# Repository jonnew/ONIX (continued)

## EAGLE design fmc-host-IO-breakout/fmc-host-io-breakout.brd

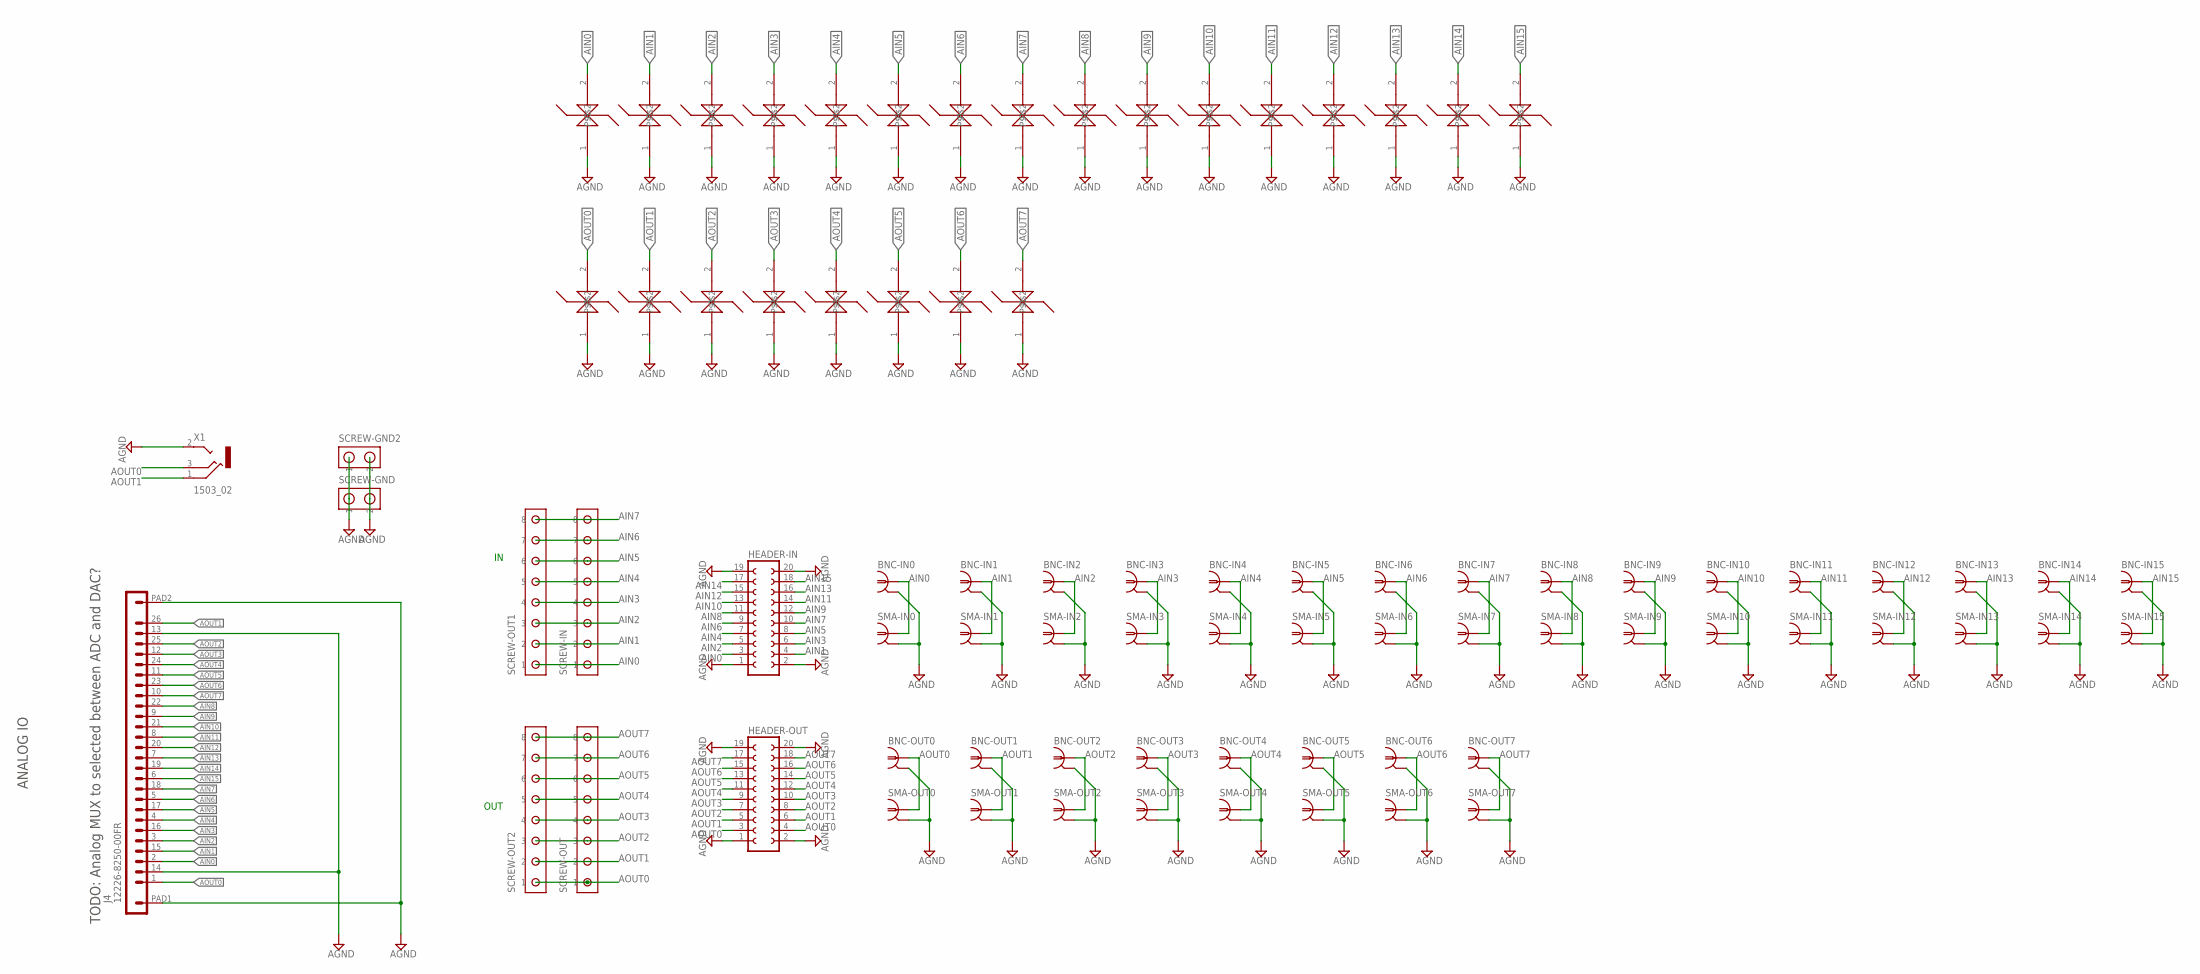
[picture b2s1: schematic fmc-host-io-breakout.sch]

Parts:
BNC-IN0, BNC-IN1, BNC-IN2, BNC-IN3, BNC-IN4, BNC-IN5, BNC-IN6, BNC-IN7, BNC-IN8, BNC-IN9, BNC-IN10, BNC-IN11, BNC-IN12, BNC-IN13, BNC-IN14, BNC-IN15: COAX_B35N61; B35N61
BNC-OUT0, BNC-OUT1, BNC-OUT2, BNC-OUT3, BNC-OUT4, BNC-OUT5, BNC-OUT6, BNC-OUT7: COAX_B35N61; B35N61
HEADER-IN: FE10-2
HEADER-OUT: FE10-2
J4: 12226-8250-00FR; 12226-82X0-00XX
SCREW-GND, SCREW-GND2: SCREW2
SCREW-IN: SCREW8
SCREW-OUT, SCREW-OUT1, SCREW-OUT2: SCREW8
SMA-IN0, SMA-IN1, SMA-IN2, SMA-IN3, SMA-IN4, SMA-IN5, SMA-IN6, SMA-IN7, SMA-IN8, SMA-IN9, SMA-IN10, SMA-IN11, SMA-IN12, SMA-IN13, SMA-IN14, SMA-IN15: COAX_SMA-VERT; SMA_JACK_142-0701-201
SMA-OUT0, SMA-OUT1, SMA-OUT2, SMA-OUT3, SMA-OUT4, SMA-OUT5, SMA-OUT6, SMA-OUT7: COAX_SMA-VERT; SMA_JACK_142-0701-201
U$1, U$2, U$3, U$4, U$5, U$6, U$7, U$8, U$9, U$10, U$11, U$12, U$13, U$14, U$15, U$16, U$17, U$18, U$19, U$20, U$21, U$22, U$23, U$24: DIODE-ESD-BIDIRECTIONALDO-214AA; DIOC7026X260
X1: 1503_02

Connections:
AIN0: BNC-IN0.1, HEADER-IN.3, J4.2, SCREW-IN.1, SCREW-OUT1.1, SMA-IN0.CLK (1), U$1.2
AIN1: BNC-IN1.1, HEADER-IN.4, J4.15, SCREW-IN.2, SCREW-OUT1.2, SMA-IN1.CLK (1), U$2.2
AIN2: BNC-IN2.1, HEADER-IN.5, J4.3, SCREW-IN.3, SCREW-OUT1.3, SMA-IN2.CLK (1), U$3.2
AIN3: BNC-IN3.1, HEADER-IN.6, J4.16, SCREW-IN.4, SCREW-OUT1.4, SMA-IN3.CLK (1), U$4.2
AIN4: BNC-IN4.1, HEADER-IN.7, J4.4, SCREW-IN.5, SCREW-OUT1.5, SMA-IN4.CLK (1), U$5.2
AIN5: BNC-IN5.1, HEADER-IN.8, J4.17, SCREW-IN.6, SCREW-OUT1.6, SMA-IN5.CLK (1), U$6.2
AIN6: BNC-IN6.1, HEADER-IN.9, J4.5, SCREW-IN.7, SCREW-OUT1.7, SMA-IN6.CLK (1), U$7.2
AIN7: BNC-IN7.1, HEADER-IN.10, J4.18, SCREW-IN.8, SCREW-OUT1.8, SMA-IN7.CLK (1), U$8.2
AIN8: BNC-IN8.1, HEADER-IN.11, J4.22, SMA-IN8.CLK (1), U$17.2
AIN9: BNC-IN9.1, HEADER-IN.12, J4.9, SMA-IN9.CLK (1), U$18.2
AIN10: BNC-IN10.1, HEADER-IN.13, J4.21, SMA-IN10.CLK (1), U$19.2
AIN11: BNC-IN11.1, HEADER-IN.14, J4.8, SMA-IN11.CLK (1), U$20.2
AIN12: BNC-IN12.1, HEADER-IN.15, J4.20, SMA-IN12.CLK (1), U$21.2
AIN13: BNC-IN13.1, HEADER-IN.16, J4.7, SMA-IN13.CLK (1), U$22.2
AIN14: BNC-IN14.1, HEADER-IN.17, J4.19, SMA-IN14.CLK (1), U$23.2
AIN15: BNC-IN15.1, HEADER-IN.18, J4.6, SMA-IN15.CLK (1), U$24.2
AOUT0: BNC-OUT0.1, HEADER-OUT.3, HEADER-OUT.4, J4.1, SCREW-OUT.1, SCREW-OUT2.1, SMA-OUT0.CLK (1), U$9.2, X1.3
AOUT1: BNC-OUT1.1, HEADER-OUT.5, HEADER-OUT.6, J4.26, SCREW-OUT.2, SCREW-OUT2.2, SMA-OUT1.CLK (1), U$10.2, X1.1
AOUT2: BNC-OUT2.1, HEADER-OUT.7, HEADER-OUT.8, J4.25, SCREW-OUT.3, SCREW-OUT2.3, SMA-OUT2.CLK (1), U$11.2
AOUT3: BNC-OUT3.1, HEADER-OUT.9, HEADER-OUT.10, J4.12, SCREW-OUT.4, SCREW-OUT2.4, SMA-OUT3.CLK (1), U$12.2
AOUT4: BNC-OUT4.1, HEADER-OUT.11, HEADER-OUT.12, J4.24, SCREW-OUT.5, SCREW-OUT2.5, SMA-OUT4.CLK (1), U$13.2
AOUT5: BNC-OUT5.1, HEADER-OUT.13, HEADER-OUT.14, J4.11, SCREW-OUT.6, SCREW-OUT2.6, SMA-OUT5.CLK (1), U$14.2
AOUT6: BNC-OUT6.1, HEADER-OUT.15, HEADER-OUT.16, J4.23, SCREW-OUT.7, SCREW-OUT2.7, SMA-OUT6.CLK (1), U$15.2
AOUT7: BNC-OUT7.1, HEADER-OUT.17, HEADER-OUT.18, J4.10, SCREW-OUT.8, SCREW-OUT2.8, SMA-OUT7.CLK (1), U$16.2
GND: BNC-IN0.2, BNC-IN0.3 (2), BNC-IN0.4 (2), BNC-IN0.5 (2), BNC-IN1.2, BNC-IN1.3 (2), BNC-IN1.4 (2), BNC-IN1.5 (2), BNC-IN2.2, BNC-IN2.3 (2), BNC-IN2.4 (2), BNC-IN2.5 (2), BNC-IN3.2, BNC-IN3.3 (2), BNC-IN3.4 (2), BNC-IN3.5 (2), BNC-IN4.2, BNC-IN4.3 (2), BNC-IN4.4 (2), BNC-IN4.5 (2), BNC-IN5.2, BNC-IN5.3 (2), BNC-IN5.4 (2), BNC-IN5.5 (2), BNC-IN6.2, BNC-IN6.3 (2), BNC-IN6.4 (2), BNC-IN6.5 (2), BNC-IN7.2, BNC-IN7.3 (2), BNC-IN7.4 (2), BNC-IN7.5 (2), BNC-IN8.2, BNC-IN8.3 (2), BNC-IN8.4 (2), BNC-IN8.5 (2), BNC-IN9.2, BNC-IN9.3 (2), BNC-IN9.4 (2), BNC-IN9.5 (2), BNC-IN10.2, BNC-IN10.3 (2), BNC-IN10.4 (2), BNC-IN10.5 (2), BNC-IN11.2, BNC-IN11.3 (2), BNC-IN11.4 (2), BNC-IN11.5 (2), BNC-IN12.2, BNC-IN12.3 (2), BNC-IN12.4 (2), BNC-IN12.5 (2), BNC-IN13.2, BNC-IN13.3 (2), BNC-IN13.4 (2), BNC-IN13.5 (2), BNC-IN14.2, BNC-IN14.3 (2), BNC-IN14.4 (2), BNC-IN14.5 (2), BNC-IN15.2, BNC-IN15.3 (2), BNC-IN15.4 (2), BNC-IN15.5 (2), BNC-OUT0.2, BNC-OUT0.3 (2), BNC-OUT0.4 (2), BNC-OUT0.5 (2), BNC-OUT1.2, BNC-OUT1.3 (2), BNC-OUT1.4 (2), BNC-OUT1.5 (2), BNC-OUT2.2, BNC-OUT2.3 (2), BNC-OUT2.4 (2), BNC-OUT2.5 (2), BNC-OUT3.2, BNC-OUT3.3 (2), BNC-OUT3.4 (2), BNC-OUT3.5 (2), BNC-OUT4.2, BNC-OUT4.3 (2), BNC-OUT4.4 (2), BNC-OUT4.5 (2), BNC-OUT5.2, BNC-OUT5.3 (2), BNC-OUT5.4 (2), BNC-OUT5.5 (2), BNC-OUT6.2, BNC-OUT6.3 (2), BNC-OUT6.4 (2), BNC-OUT6.5 (2), BNC-OUT7.2, BNC-OUT7.3 (2), BNC-OUT7.4 (2), BNC-OUT7.5 (2), HEADER-IN.1, HEADER-IN.2, HEADER-IN.19, HEADER-IN.20, HEADER-OUT.1, HEADER-OUT.2, HEADER-OUT.19, HEADER-OUT.20, J4.13, J4.14, J4.PAD1, J4.PAD2, SCREW-GND.P$1 (1), SCREW-GND.P$2 (2), SCREW-GND2.P$1 (1), SCREW-GND2.P$2 (2), SMA-IN0.GND$1 (2), SMA-IN0.GND$2 (2), SMA-IN0.GND$3 (2), SMA-IN0.GND$4 (2), SMA-IN1.GND$1 (2), SMA-IN1.GND$2 (2), SMA-IN1.GND$3 (2), SMA-IN1.GND$4 (2), SMA-IN2.GND$1 (2), SMA-IN2.GND$2 (2), SMA-IN2.GND$3 (2), SMA-IN2.GND$4 (2), SMA-IN3.GND$1 (2), SMA-IN3.GND$2 (2), SMA-IN3.GND$3 (2), SMA-IN3.GND$4 (2), SMA-IN4.GND$1 (2), SMA-IN4.GND$2 (2), SMA-IN4.GND$3 (2), SMA-IN4.GND$4 (2), SMA-IN5.GND$1 (2), SMA-IN5.GND$2 (2), SMA-IN5.GND$3 (2), SMA-IN5.GND$4 (2), SMA-IN6.GND$1 (2), SMA-IN6.GND$2 (2), SMA-IN6.GND$3 (2), SMA-IN6.GND$4 (2), SMA-IN7.GND$1 (2), SMA-IN7.GND$2 (2), SMA-IN7.GND$3 (2), SMA-IN7.GND$4 (2), SMA-IN8.GND$1 (2), SMA-IN8.GND$2 (2), SMA-IN8.GND$3 (2), SMA-IN8.GND$4 (2), SMA-IN9.GND$1 (2), SMA-IN9.GND$2 (2), SMA-IN9.GND$3 (2), SMA-IN9.GND$4 (2), SMA-IN10.GND$1 (2), SMA-IN10.GND$2 (2), SMA-IN10.GND$3 (2), SMA-IN10.GND$4 (2), SMA-IN11.GND$1 (2), SMA-IN11.GND$2 (2), SMA-IN11.GND$3 (2), SMA-IN11.GND$4 (2), SMA-IN12.GND$1 (2), SMA-IN12.GND$2 (2), SMA-IN12.GND$3 (2), SMA-IN12.GND$4 (2), SMA-IN13.GND$1 (2), SMA-IN13.GND$2 (2), SMA-IN13.GND$3 (2), SMA-IN13.GND$4 (2), SMA-IN14.GND$1 (2), SMA-IN14.GND$2 (2), SMA-IN14.GND$3 (2), SMA-IN14.GND$4 (2), SMA-IN15.GND$1 (2), SMA-IN15.GND$2 (2), SMA-IN15.GND$3 (2), SMA-IN15.GND$4 (2), SMA-OUT0.GND$1 (2), SMA-OUT0.GND$2 (2), SMA-OUT0.GND$3 (2), SMA-OUT0.GND$4 (2), SMA-OUT1.GND$1 (2), SMA-OUT1.GND$2 (2), SMA-OUT1.GND$3 (2), SMA-OUT1.GND$4 (2), SMA-OUT2.GND$1 (2), SMA-OUT2.GND$2 (2), SMA-OUT2.GND$3 (2), SMA-OUT2.GND$4 (2), SMA-OUT3.GND$1 (2), SMA-OUT3.GND$2 (2), SMA-OUT3.GND$3 (2), SMA-OUT3.GND$4 (2), SMA-OUT4.GND$1 (2), SMA-OUT4.GND$2 (2), SMA-OUT4.GND$3 (2), SMA-OUT4.GND$4 (2), SMA-OUT5.GND$1 (2), SMA-OUT5.GND$2 (2), SMA-OUT5.GND$3 (2), SMA-OUT5.GND$4 (2), SMA-OUT6.GND$1 (2), SMA-OUT6.GND$2 (2), SMA-OUT6.GND$3 (2), SMA-OUT6.GND$4 (2), SMA-OUT7.GND$1 (2), SMA-OUT7.GND$2 (2), SMA-OUT7.GND$3 (2), SMA-OUT7.GND$4 (2), U$1.1, U$2.1, U$3.1, U$4.1, U$5.1, U$6.1, U$7.1, U$8.1, U$9.1, U$10.1, U$11.1, U$12.1, U$13.1, U$14.1, U$15.1, U$16.1, U$17.1, U$18.1, U$19.1, U$20.1, U$21.1, U$22.1, U$23.1, U$24.1, X1.2

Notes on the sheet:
TODO: Analog MUX to selected between ADC and DAC?
ANALOG IO
OUT

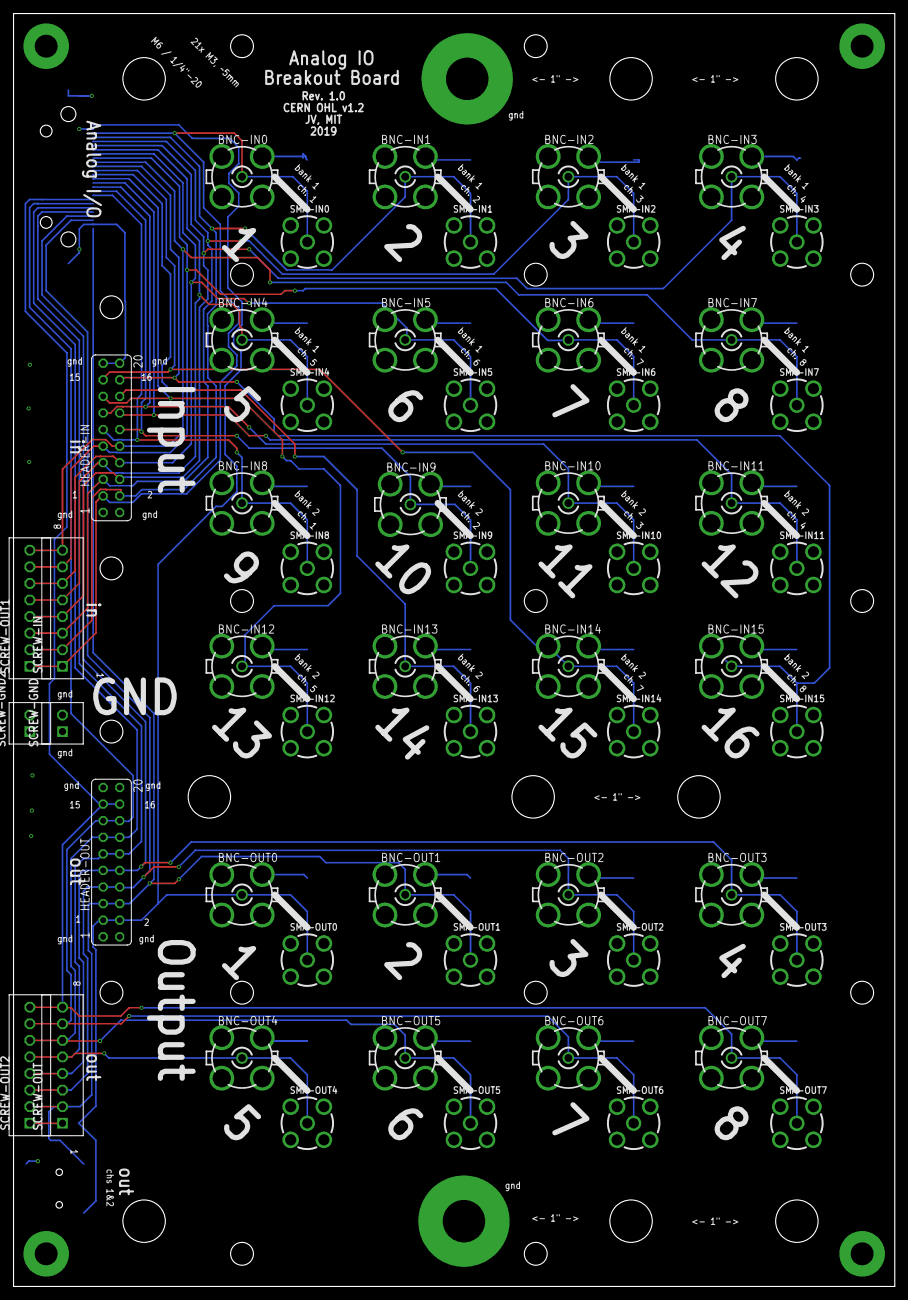
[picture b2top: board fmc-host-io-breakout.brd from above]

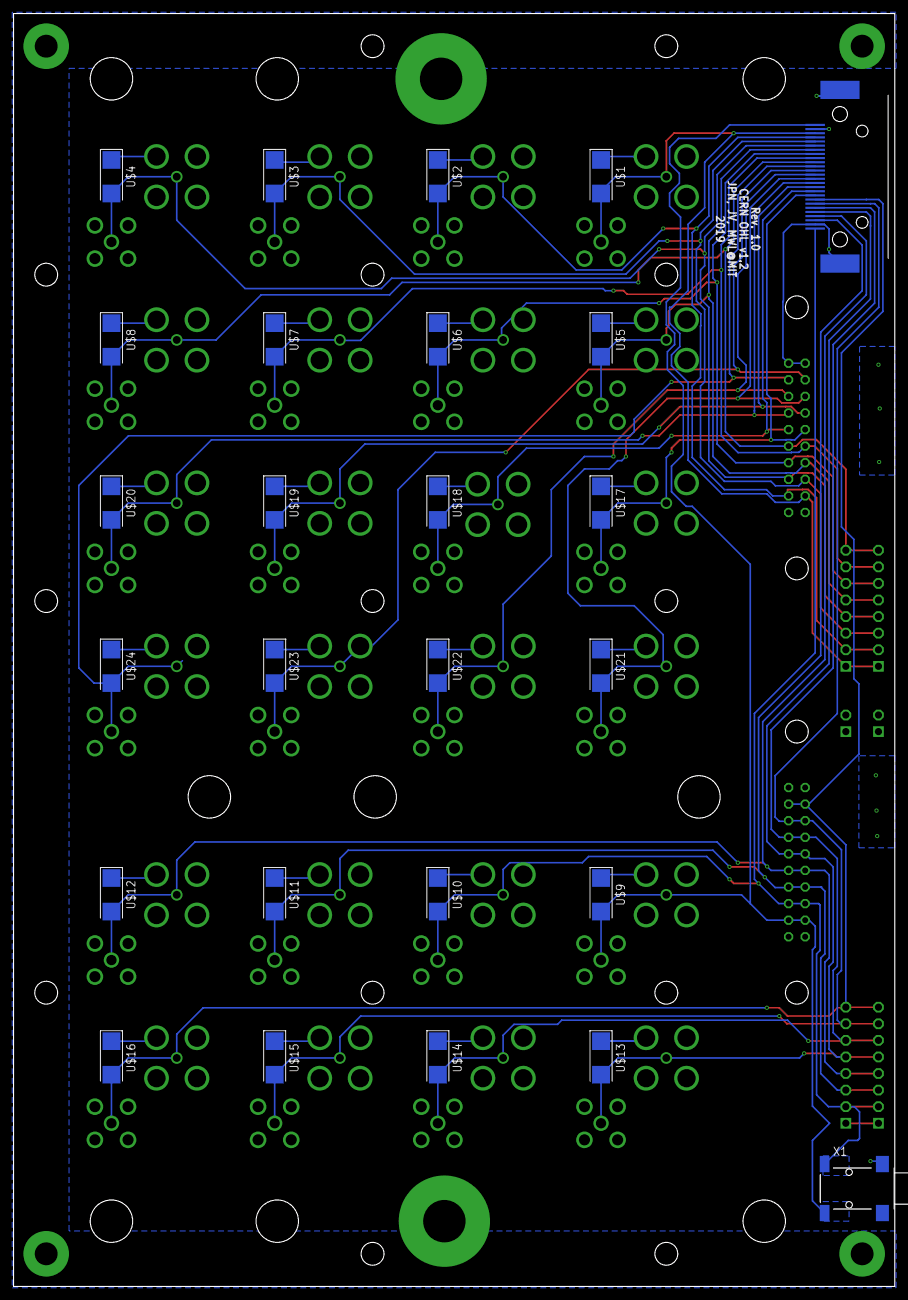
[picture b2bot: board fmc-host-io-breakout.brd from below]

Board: 2 copper layers, 135.0 x 195.0 mm, 82 parts (26 on the bottom side), 25 nets.

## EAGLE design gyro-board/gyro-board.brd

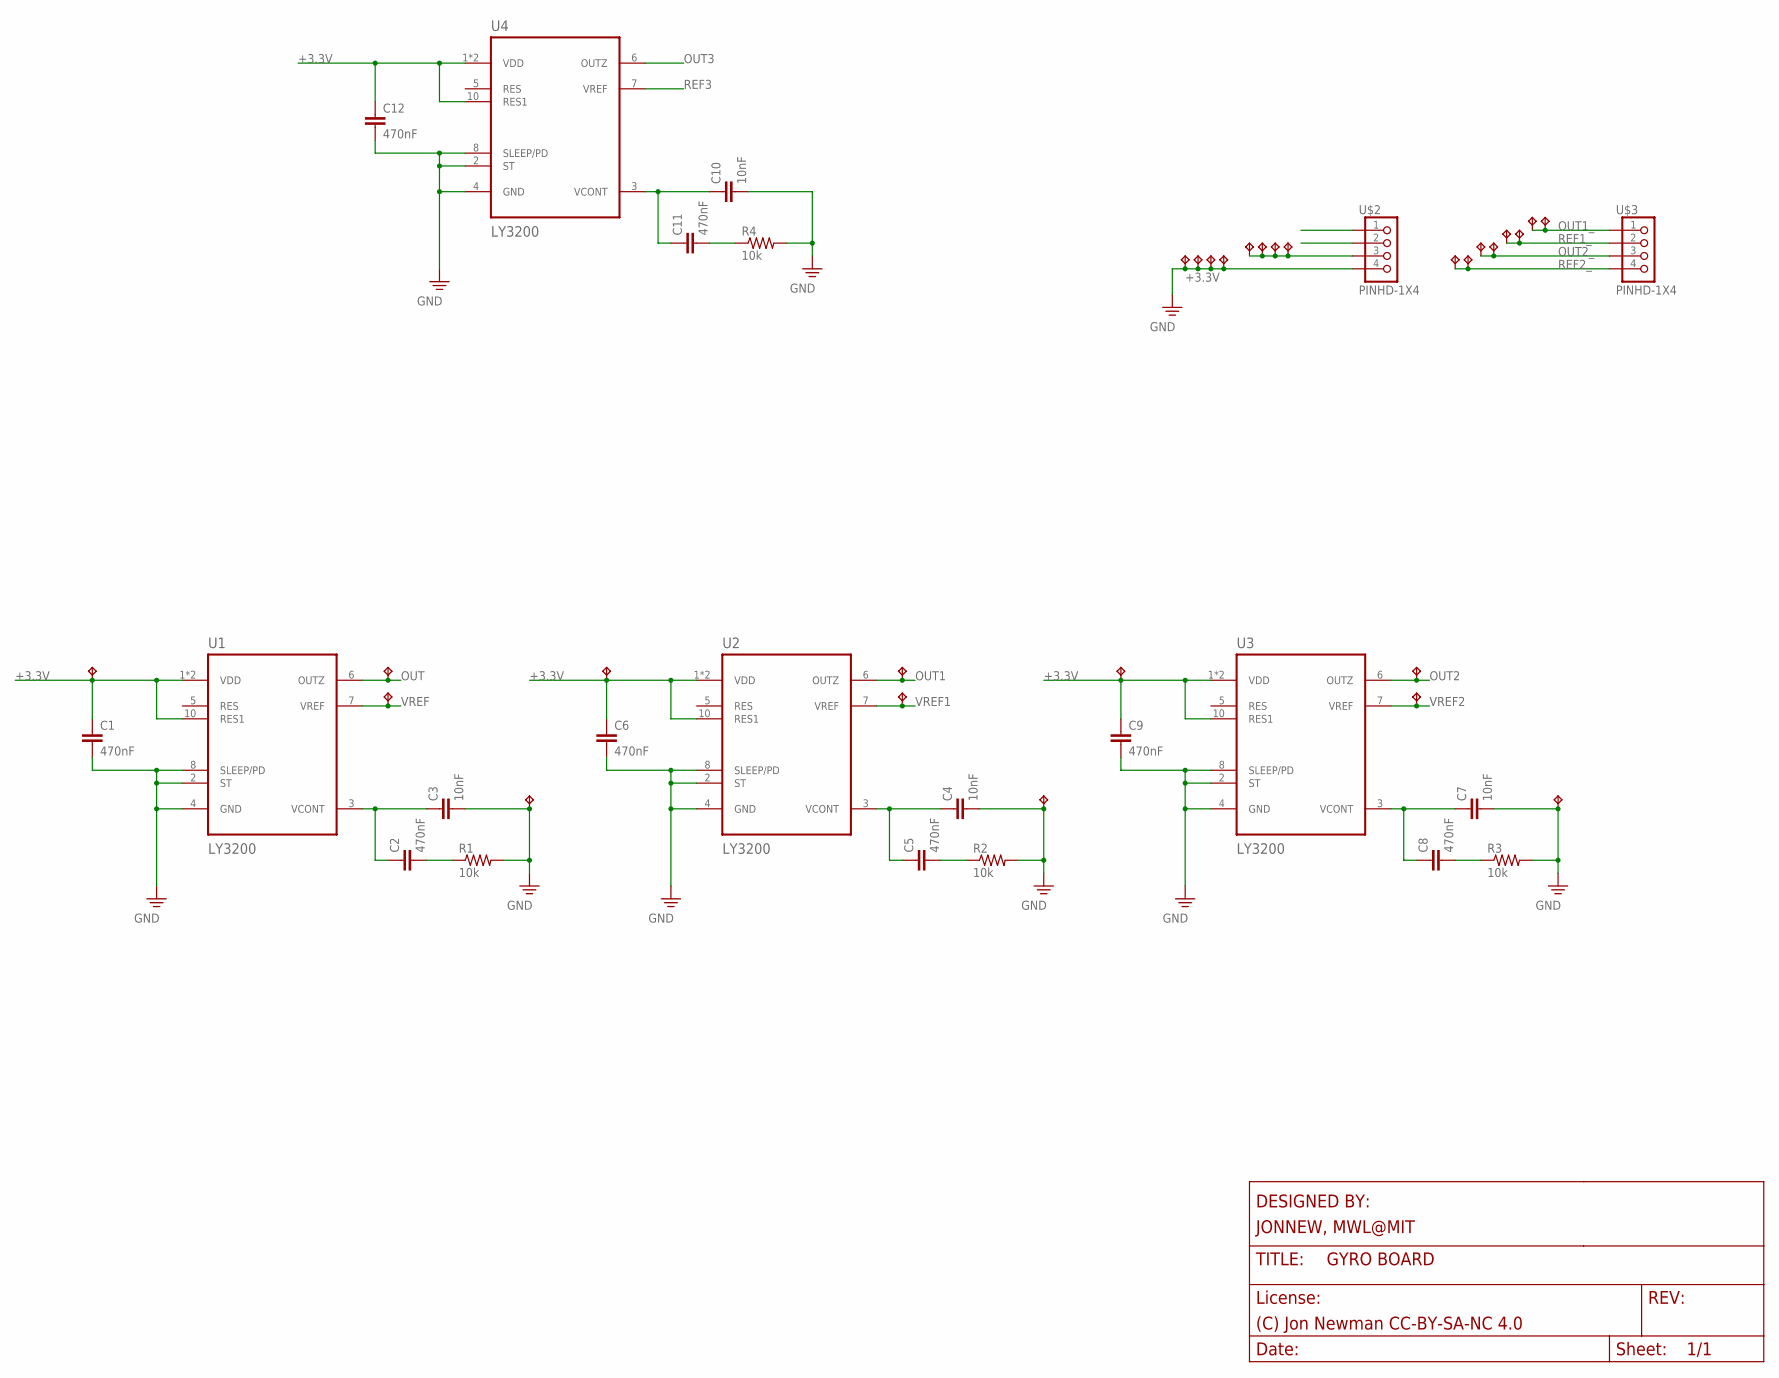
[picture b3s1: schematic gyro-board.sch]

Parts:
C1, C2, C5, C6, C8, C9, C11, C12: 470nF; 0201
C3, C4, C7, C10: 10nF; 0201
R1, R2, R3, R4: 10k; 0201
TP1, TP2, TP3, TP4, TP5, TP6, TP7, TP8, TP9, TP10, TP11, TP12, TP13, TP14, TP15, TP16, TP17, TP18, TP19, TP20, TP21, TP22, TP23, TP24, TP25, TP26, TP27, TP28: TPTP08SQ; TP08SQ
U1, U2, U3, U4: LY3200; LGA-10-COMPACT
U$2, U$3: PINHD-1X4; 1X04

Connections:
+3.3V: C1.1, C6.1, C9.1, C12.1, TP1.TP, TP4.TP, TP9.TP, TP25.TP, TP26.TP, TP27.TP, TP28.TP, U1.1 (VDD), U1.9 (VDD), U1.10 (RES1), U2.1 (VDD), U2.9 (VDD), U2.10 (RES1), U3.1 (VDD), U3.9 (VDD), U3.10 (RES1), U4.1 (VDD), U4.9 (VDD), U4.10 (RES1), U$2.3
GND: C1.2, C3.2, C4.2, C6.2, C7.2, C9.2, C10.2, C12.2, R1.2, R2.2, R3.2, R4.2, TP3.TP, TP7.TP, TP11.TP, TP13.TP, TP22.TP, TP23.TP, TP24.TP, U1.2 (ST), U1.4 (GND), U1.8 (SLEEP/PD), U2.2 (ST), U2.4 (GND), U2.8 (SLEEP/PD), U3.2 (ST), U3.4 (GND), U3.8 (SLEEP/PD), U4.2 (ST), U4.4 (GND), U4.8 (SLEEP/PD), U$2.4
unnamed: C4.1, C5.1, U2.3 (VCONT)
unnamed: C5.2, R2.1
unnamed: C2.1, C3.1, U1.3 (VCONT)
unnamed: C2.2, R1.1
unnamed: C7.1, C8.1, U3.3 (VCONT)
unnamed: C8.2, R3.1
unnamed: C10.1, C11.1, U4.3 (VCONT)
unnamed: C11.2, R4.1
OUT: TP2.TP, U1.6 (OUTZ)
OUT1: TP6.TP, U2.6 (OUTZ)
OUT1_: TP20.TP, TP21.TP, U$3.1
OUT2: TP10.TP, U3.6 (OUTZ)
OUT2_: TP16.TP, TP17.TP, U$3.3
OUT3: U4.6 (OUTZ), U$2.1
REF1_: TP18.TP, TP19.TP, U$3.2
REF2_: TP14.TP, TP15.TP, U$3.4
REF3: U4.7 (VREF), U$2.2
VREF: TP5.TP, U1.7 (VREF)
VREF1: TP8.TP, U2.7 (VREF)
VREF2: TP12.TP, U3.7 (VREF)

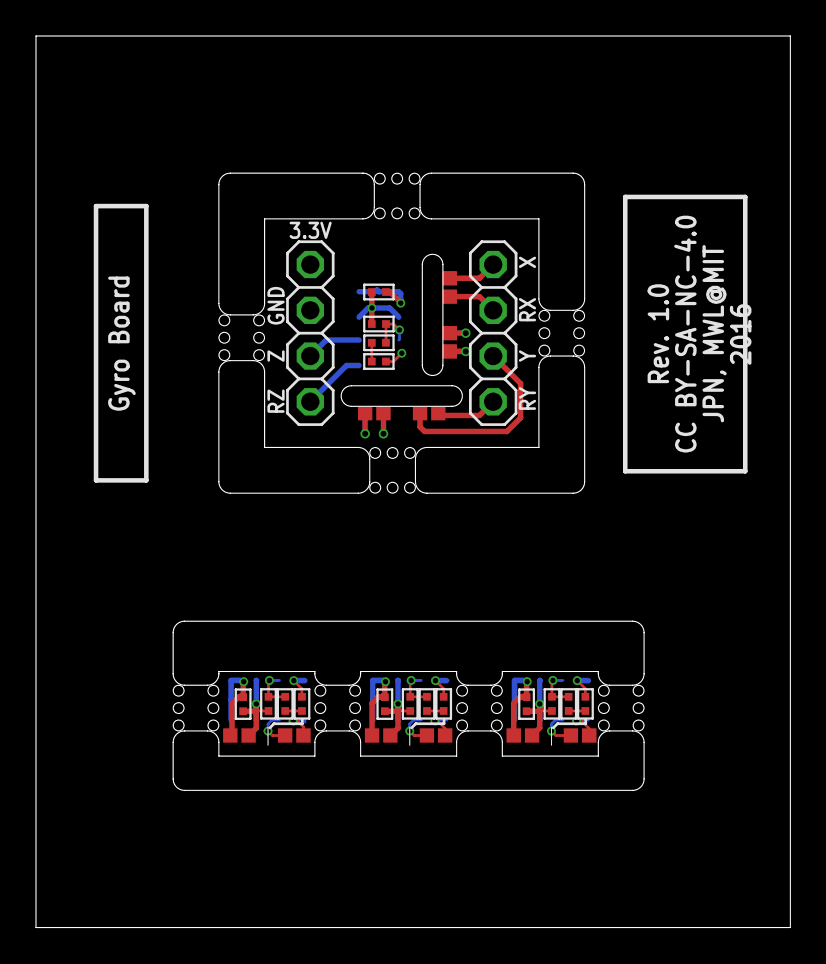
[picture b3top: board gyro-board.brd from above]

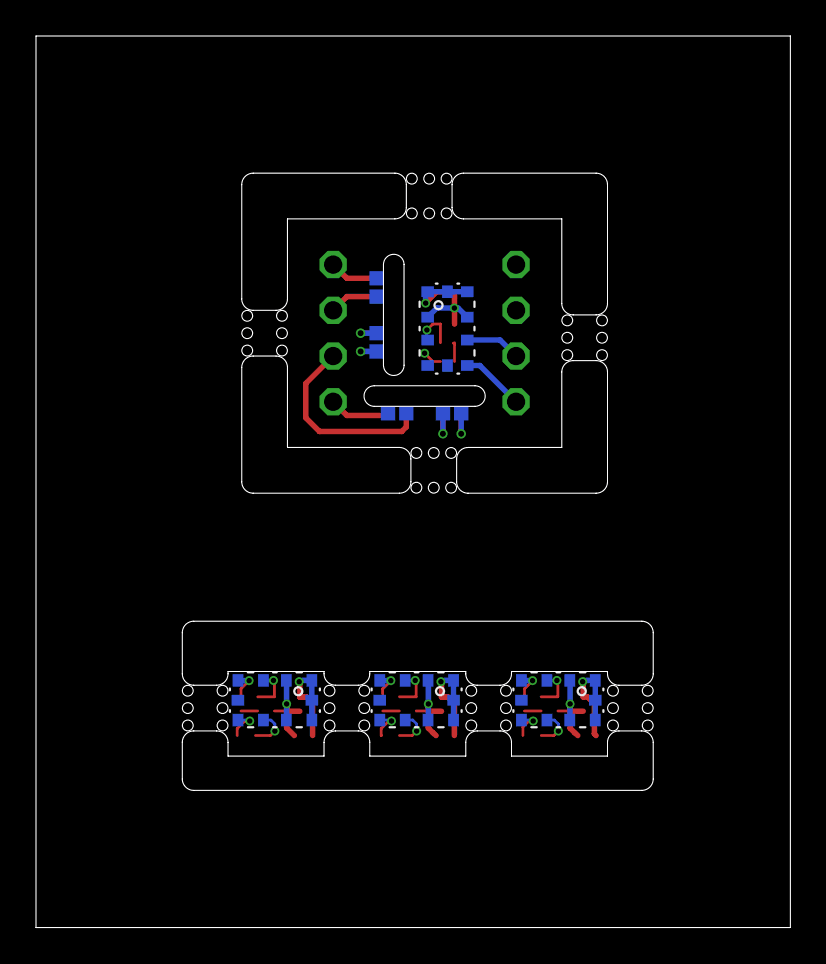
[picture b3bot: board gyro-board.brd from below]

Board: 4 copper layers, 41.9 x 49.5 mm, 50 parts (12 on the bottom side), 22 nets.

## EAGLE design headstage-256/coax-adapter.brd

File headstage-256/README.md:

# headstage-256
Serialized, multifunction headstage for large rodents. Supports both 128 or 256
channels. Designed to interface with [eib-128](../eib-128/README.md) or
[eib-256](../eib-256/README.md)

## Schematic 

## Gerber Files
{% include gerber_layers.md %}

## Bill of Materials
The BOM is located on [this google
sheet](https://docs.google.com/spreadsheets/d/1F-KWcdvH_63iXjZf0cgCfDiFX6XXW3qw6rlR8DZrFpQ/edit#gid=1075887549)

## FPGA Pinout
The FPGA pinout is located on [this google
sheet](https://docs.google.com/spreadsheets/d/1oJoQ89dJNL9LIiTrRnwJ_9KGiLzJ53Tju5Lfchuvsb0/edit#gid=1588805600)

## Connector Pinout
The headstage connector pinouts (ADC input mapping, stimulation connections,
etc) ares are located on these google sheets:

- [eib-128 channel mapping](https://docs.google.com/spreadsheets/d/11wRDYOqHN5lPb03yUdfXfK0zvaDYsVetplaNK-R90Gg/edit#gid=663991061)
- [eib-256 channel mapping](https://docs.google.com/spreadsheets/d/11wRDYOqHN5lPb03yUdfXfK0zvaDYsVetplaNK-R90Gg/edit#gid=538743909)

## Expansion Boads
headstage-256 has two exposed headers that supply power and general purpose analog or digital IO to expand 
its functionality. Subdirectories with the prefix 'expansion` are boards that fit into these headers to 
supply various auxiliary functions. These include:

1. expansion-uphone: ultrasonic micrphone expansion board
2. expansion-long-range: large active area light house receiver board to expand 3D tracking range by several meters.
3. expansion-debug: pinout GPIO to large 0.1" pitch headers.

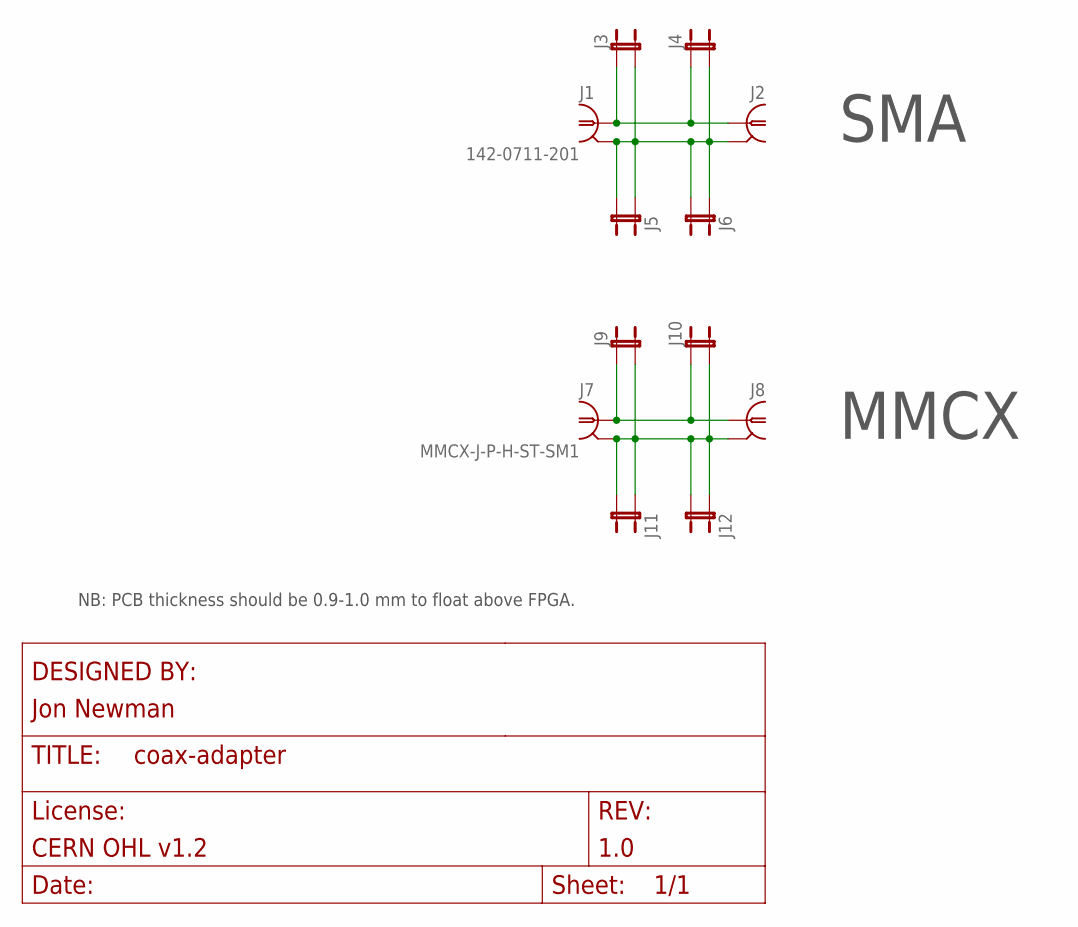
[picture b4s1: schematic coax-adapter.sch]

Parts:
J1: 142-0711-201; SMA_VERT
J2, J8: COAXCOAX-ADAPTER-8X8MM; COAX-ADAPTER-8X8MM
J3, J4, J9, J10: JP2E_COAX-ADAPTER-8X8MM-SIG; COAX-ADAPTER-8X8MM-SIG
J5, J6, J11, J12: JP2E_COAX-ADAPTER-8X8MM-GND; COAX-ADAPTER-8X8MM-GND
J7: MMCX-J-P-H-ST-SM1; MMCX-SMT-VERT

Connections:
ADAPT_SIG: J1.SIG (1), J2.SIG (1), J2.SIGPAD (1), J3.SIG (1), J4.SIG (1), J7.SIG (1), J8.SIG (1), J8.SIGPAD (1), J9.SIG (1), J10.SIG (1)
GND: J1.G1 (2), J1.G2 (2), J1.G3 (2), J1.G4 (2), J2.GND1 (2), J2.GND2 (2), J2.GND3 (2), J2.GND4 (2), J3.GND1 (2), J3.GND2 (2), J4.GND1 (2), J4.GND2 (2), J5.GND3 (1), J5.GND4 (2), J6.GND3 (1), J6.GND4 (2), J7.GND@1 (2), J7.GND@2 (2), J7.GND@3 (2), J7.GND@4 (2), J8.GND1 (2), J8.GND2 (2), J8.GND3 (2), J8.GND4 (2), J9.GND1 (2), J9.GND2 (2), J10.GND1 (2), J10.GND2 (2), J11.GND3 (1), J11.GND4 (2), J12.GND3 (1), J12.GND4 (2)

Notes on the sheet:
MMCX
SMA
NB: PCB thickness should be 0.9-1.0 mm to float above FPGA.

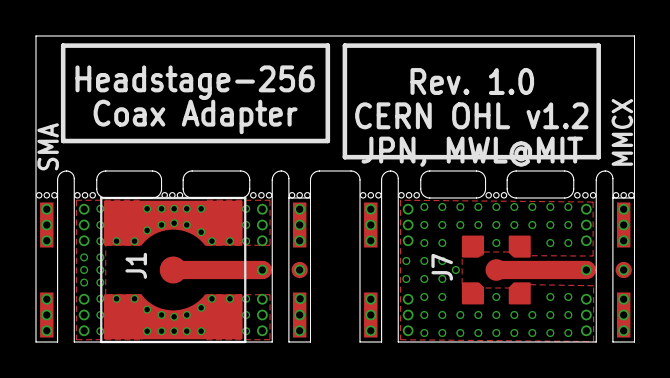
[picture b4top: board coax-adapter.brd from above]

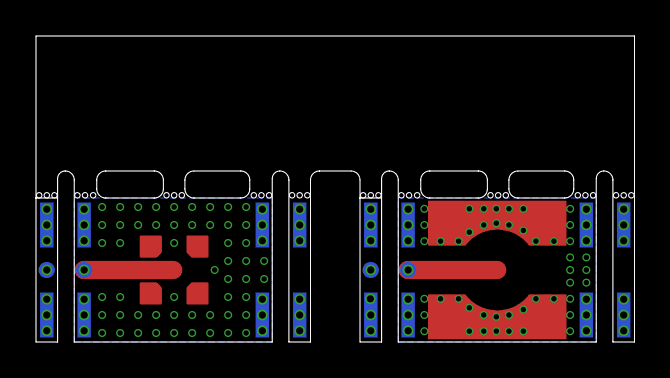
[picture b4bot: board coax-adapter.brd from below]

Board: 2 copper layers, 33.2 x 17.0 mm, 12 parts (6 on the bottom side), 2 nets.

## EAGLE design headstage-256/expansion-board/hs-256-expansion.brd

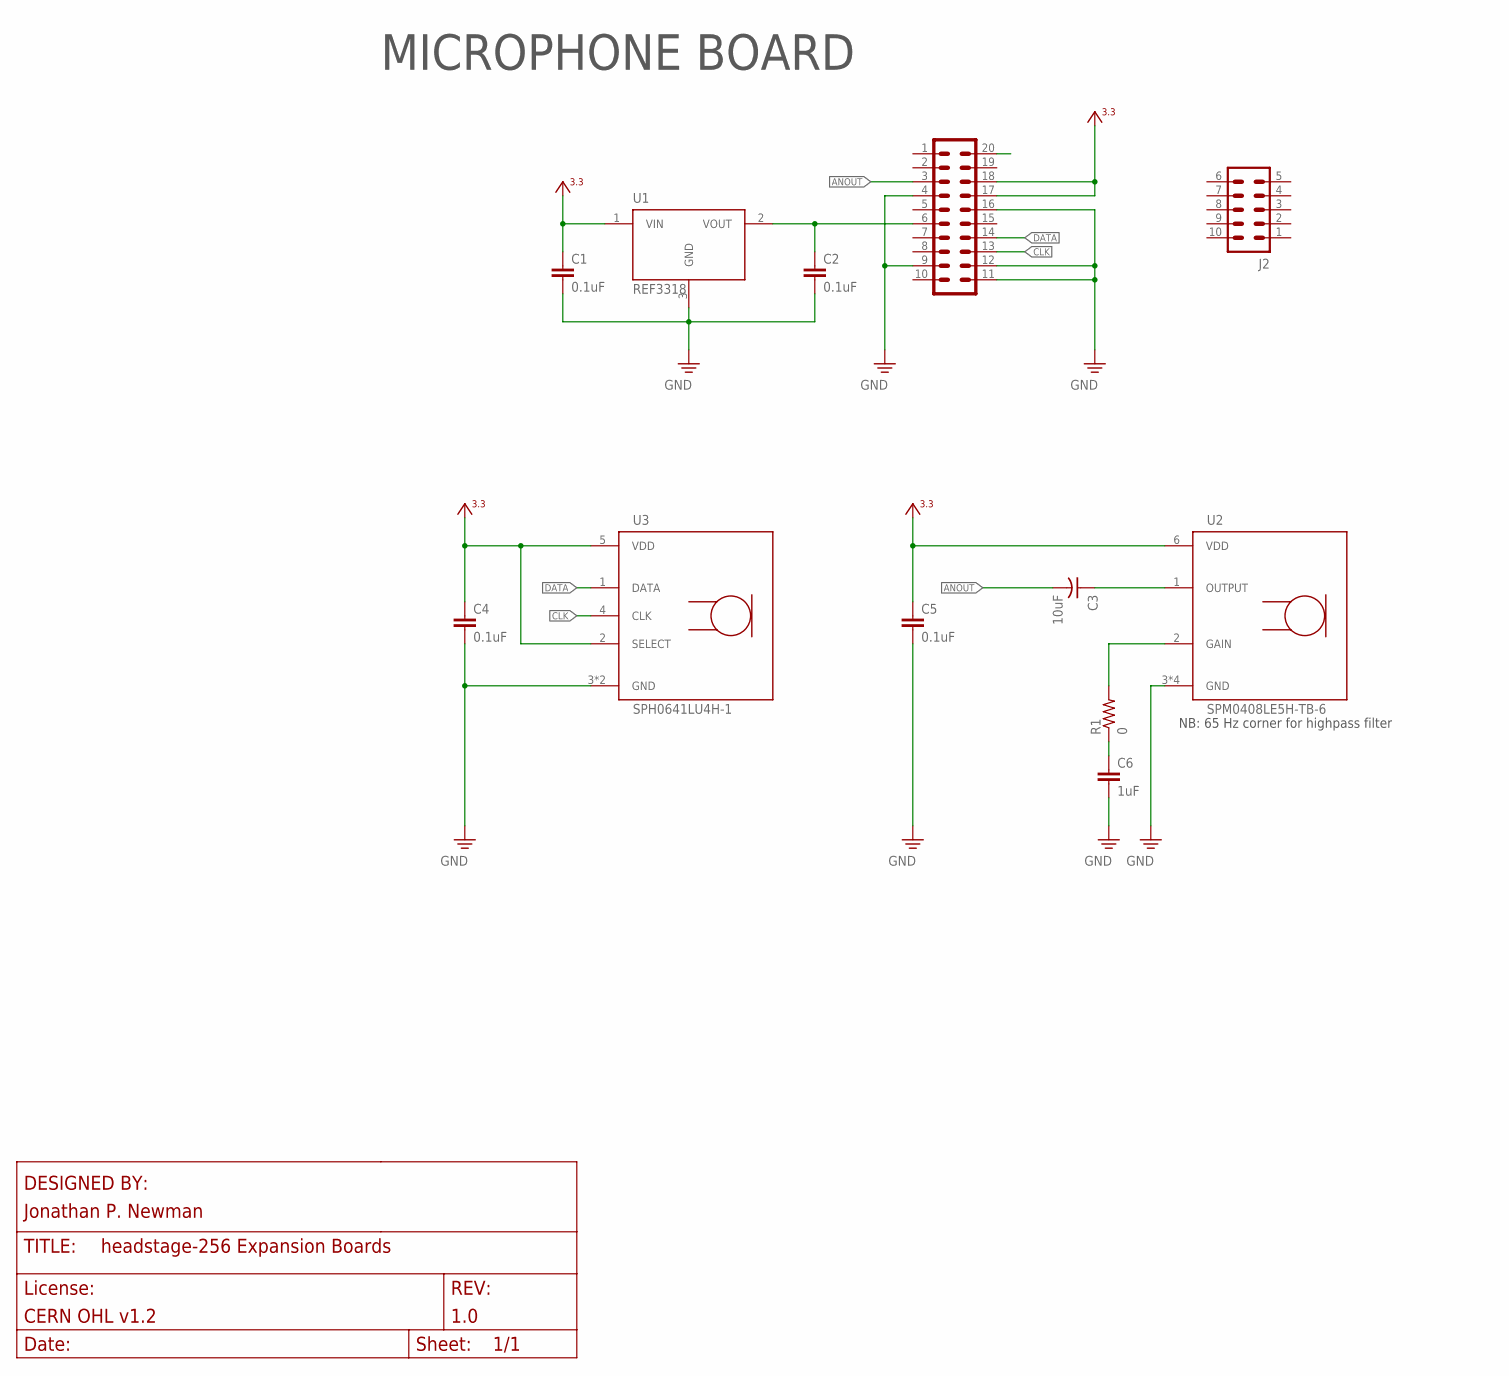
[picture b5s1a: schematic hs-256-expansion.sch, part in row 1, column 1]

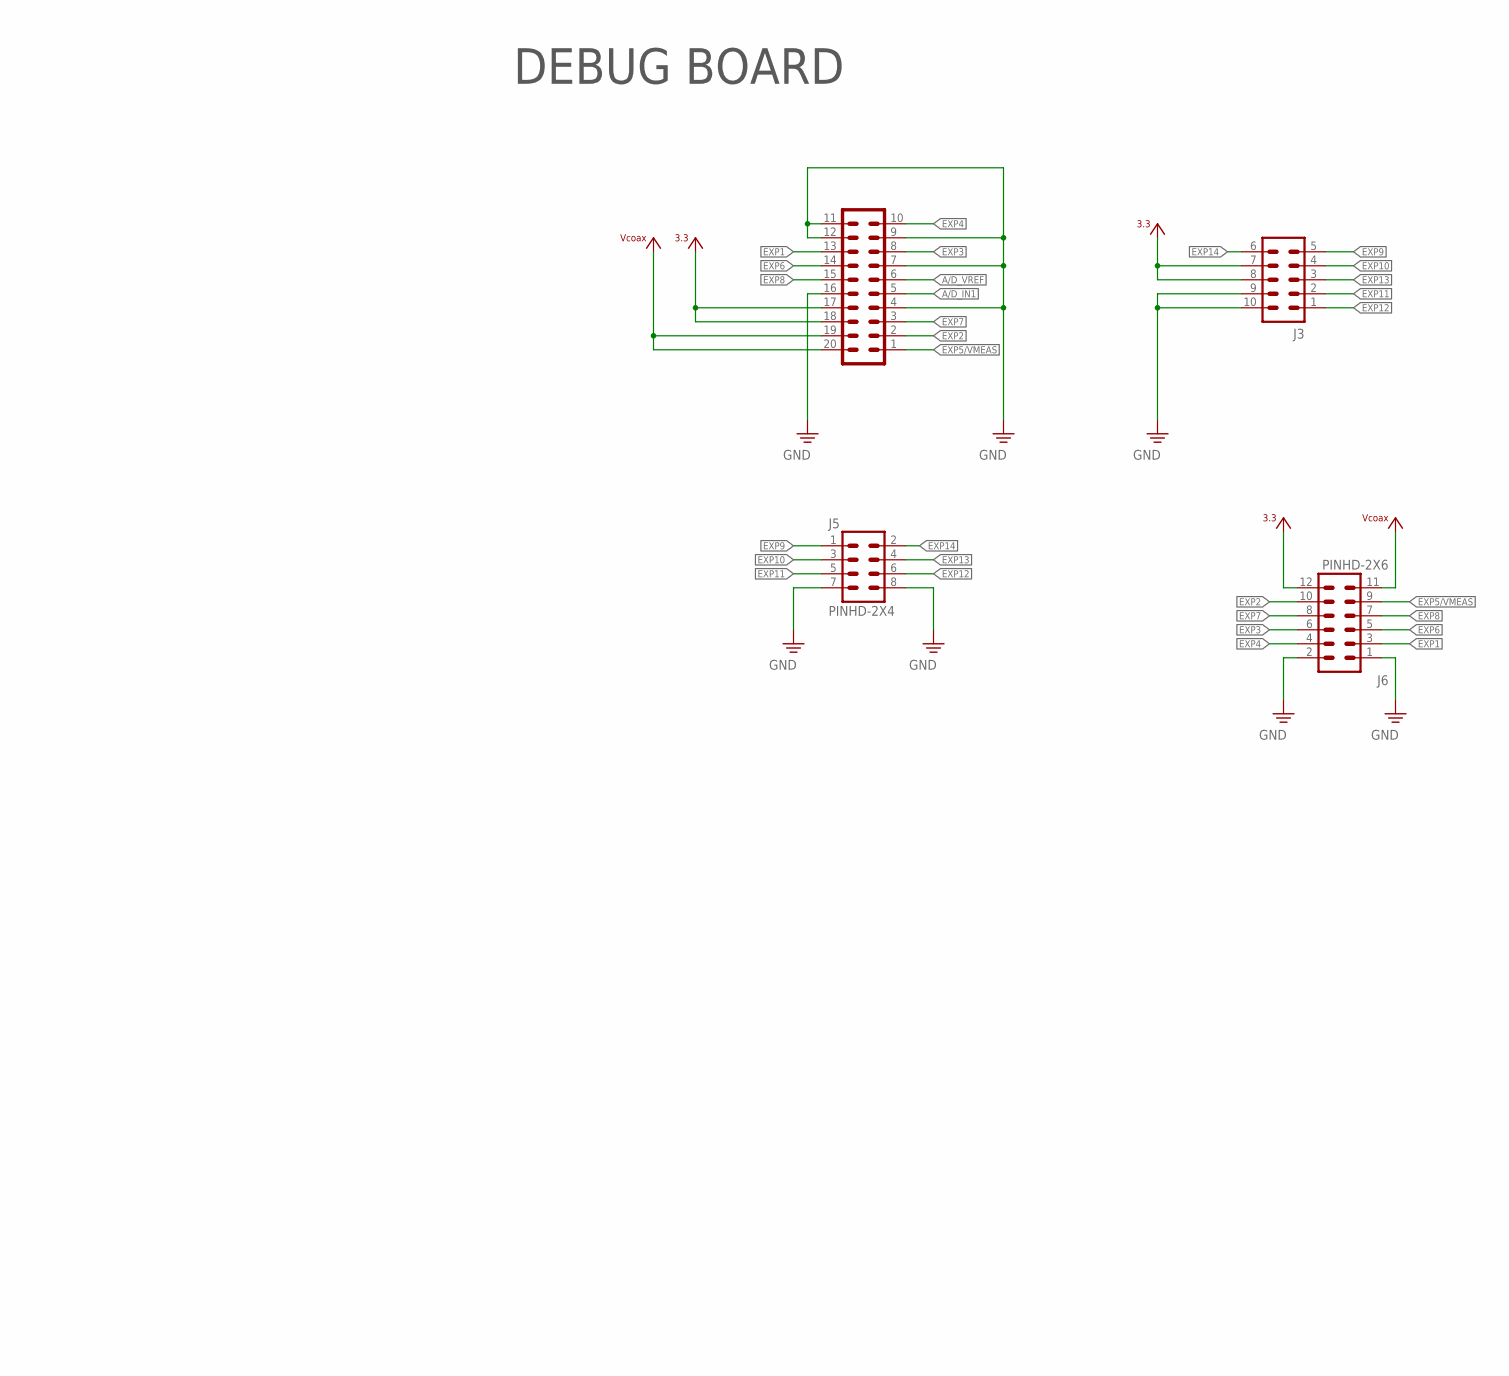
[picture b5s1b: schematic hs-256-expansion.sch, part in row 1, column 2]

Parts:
C1, C2, C4, C5: 0.1uF; 0402
C3: 10uF; 0805-POL
C6: 1uF; 0402
J1, J4: PINHD-2X10_DF40-20REC; DF40-20REC
J2, J3: PINHD-2X5_DF40-REC; DF40-10REC
J5: PINHD-2X4; 2X04-BIG
J6: PINHD-2X6; 2X06-BIG
R1: 0; 0402
U1: REF3318; SOT23
U2: SPM0408LE5H-TB-6; KNOWLES-SPM
U3: SPH0641LU4H-1; KNOWLES-SPH

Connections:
+3V3: C1.1, C4.1, C5.1, J1.17, J1.18, J3.7 (8), J3.8 (6), J4.17, J4.18, J6.12, U1.1 (VIN), U2.6 (VDD), U3.2 (SELECT), U3.5 (VDD)
A/D_IN1: J4.5
A/D_VREF: J4.6
ANOUT: C3.C (-), J1.3
CLK: J1.13, U3.4 (CLK)
DATA: J1.14, U3.1 (DATA)
EXP1: J4.13, J6.3
EXP2: J4.2, J6.10
EXP3: J4.8, J6.6
EXP4: J4.10, J6.4
EXP5/VMEAS: J4.1, J6.9
EXP6: J4.14, J6.5
EXP7: J4.3, J6.8
EXP8: J4.15, J6.7
EXP9: J3.5 (9), J5.1
EXP10: J3.4 (7), J5.3
EXP11: J3.2 (3), J5.5
EXP12: J3.1, J5.6
EXP13: J3.3 (5), J5.4
EXP14: J3.6 (10), J5.2
GND: C1.2, C2.2, C4.2, C5.2, C6.2, J1.4, J1.9, J1.11, J1.12, J1.16, J3.9 (4), J3.10 (2), J4.4, J4.7, J4.9, J4.11, J4.12, J4.16, J5.7, J5.8, J6.1, J6.2, U1.3 (GND), U2.3 (GND), U2.4 (GND), U2.5 (GND), U2.7 (GND), U3.3 (GND), U3.6 (GND)
unnamed: C6.1, R1.1
unnamed: R1.2, U2.2 (GAIN)
unnamed: C3.A (+), U2.1 (OUTPUT)
VCOAX: J4.19, J4.20, J6.11
VREF: C2.1, J1.6, U1.2 (VOUT)

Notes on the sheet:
NB: 65 Hz corner for highpass filter
DEBUG BOARD
MICROPHONE BOARD

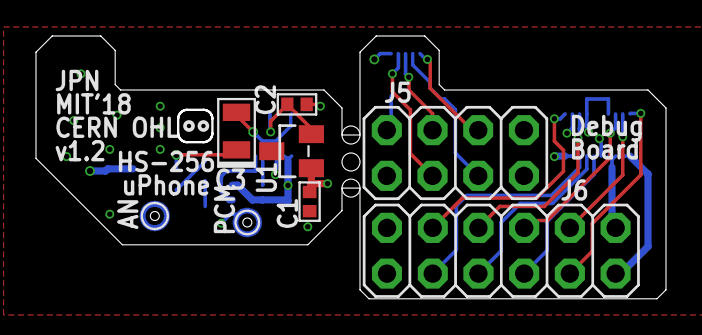
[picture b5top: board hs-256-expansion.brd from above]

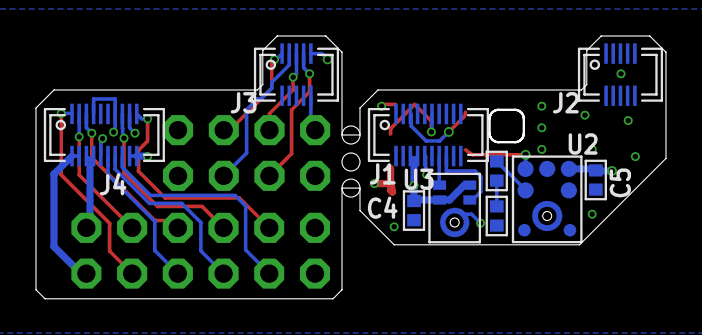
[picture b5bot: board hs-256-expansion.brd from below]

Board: 4 copper layers, 35.0 x 14.6 mm, 16 parts (10 on the bottom side), 24 nets.

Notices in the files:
fmc-host-IO-breakout/fmc-host-io-breakout.brd:
CERN OHL v1.2
fmc-host-IO-breakout/fmc-host-io-breakout.sch:
LICENSE: CERN OHL v1.2
gyro-board/gyro-board.brd:
CC BY-SA-NC-4.0
gyro-board/gyro-board.sch:
LICENSE: (C) Jon Newman CC-BY-SA-NC 4.0
headstage-256/expansion-board/hs-256-expansion.brd:
CERN OHL
